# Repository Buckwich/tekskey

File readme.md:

# Tekskey

> WIP This project is still in its prototyping phase

TODO description. Keypoints: modular, hotswap, ARGB, mirage. Usage of git submodules and stow

## Design Process

### Layout Testing with print outs

With [KLE](http://www.keyboard-layout-editor.com/) I came up with a base layout (white):

As I was unsure about the top & bottom design, I included multiple variants. The pcb version should also include support for the light gray variant (PCB A variant), which also allows to use the same pcb for left & right.

More images can be seen in [layouts/](layout/readme.md)

### Handwired 3d printed hotswap prototype

Using the [hotswap PCB generator](https://github.com/50an6xy06r6n/hotswap_pcb_generator) I printed a first prototype which I used and tested for a few weeks. The 3d printed prototype only supports the white layout.

For more renders, source and print files see [prototype](prototype/readme.md)

### QMK firmware (I'm thinking about switching to KMK)

TODO

### PCB Design

TODO

### Pull submodules

```
git submodule update --init --remote --recursive
```

https://raw.githubusercontent.com/ebastler/ebastler-KiCad-repository/main/repository.json

grid {
"name": "MX U 1/32",
"x": "0.5953125",
"y": "0.5953125"
},
{
"name": "MX U 1/24",
"x": "0.79375",
"y": "0.79375"
},
{
"name": "MX U 1/16",
"x": "1.190625",
"y": "1.190625"
},
{
"name": "MX U 1/8",
"x": "2.38125",
"y": "2.38125"
},
{
"name": "MX U 1/4",
"x": "4.7625",
"y": "4.7625"
},
{
"name": "MX U 1/2",
"x": "9.525",
"y": "9.525"
},
{
"name": "MX U 1",
"x": "19.05",
"y": "19.05"
},

TODO

check mcu mirroring

reroute edges

document lib use

find custom buckwich

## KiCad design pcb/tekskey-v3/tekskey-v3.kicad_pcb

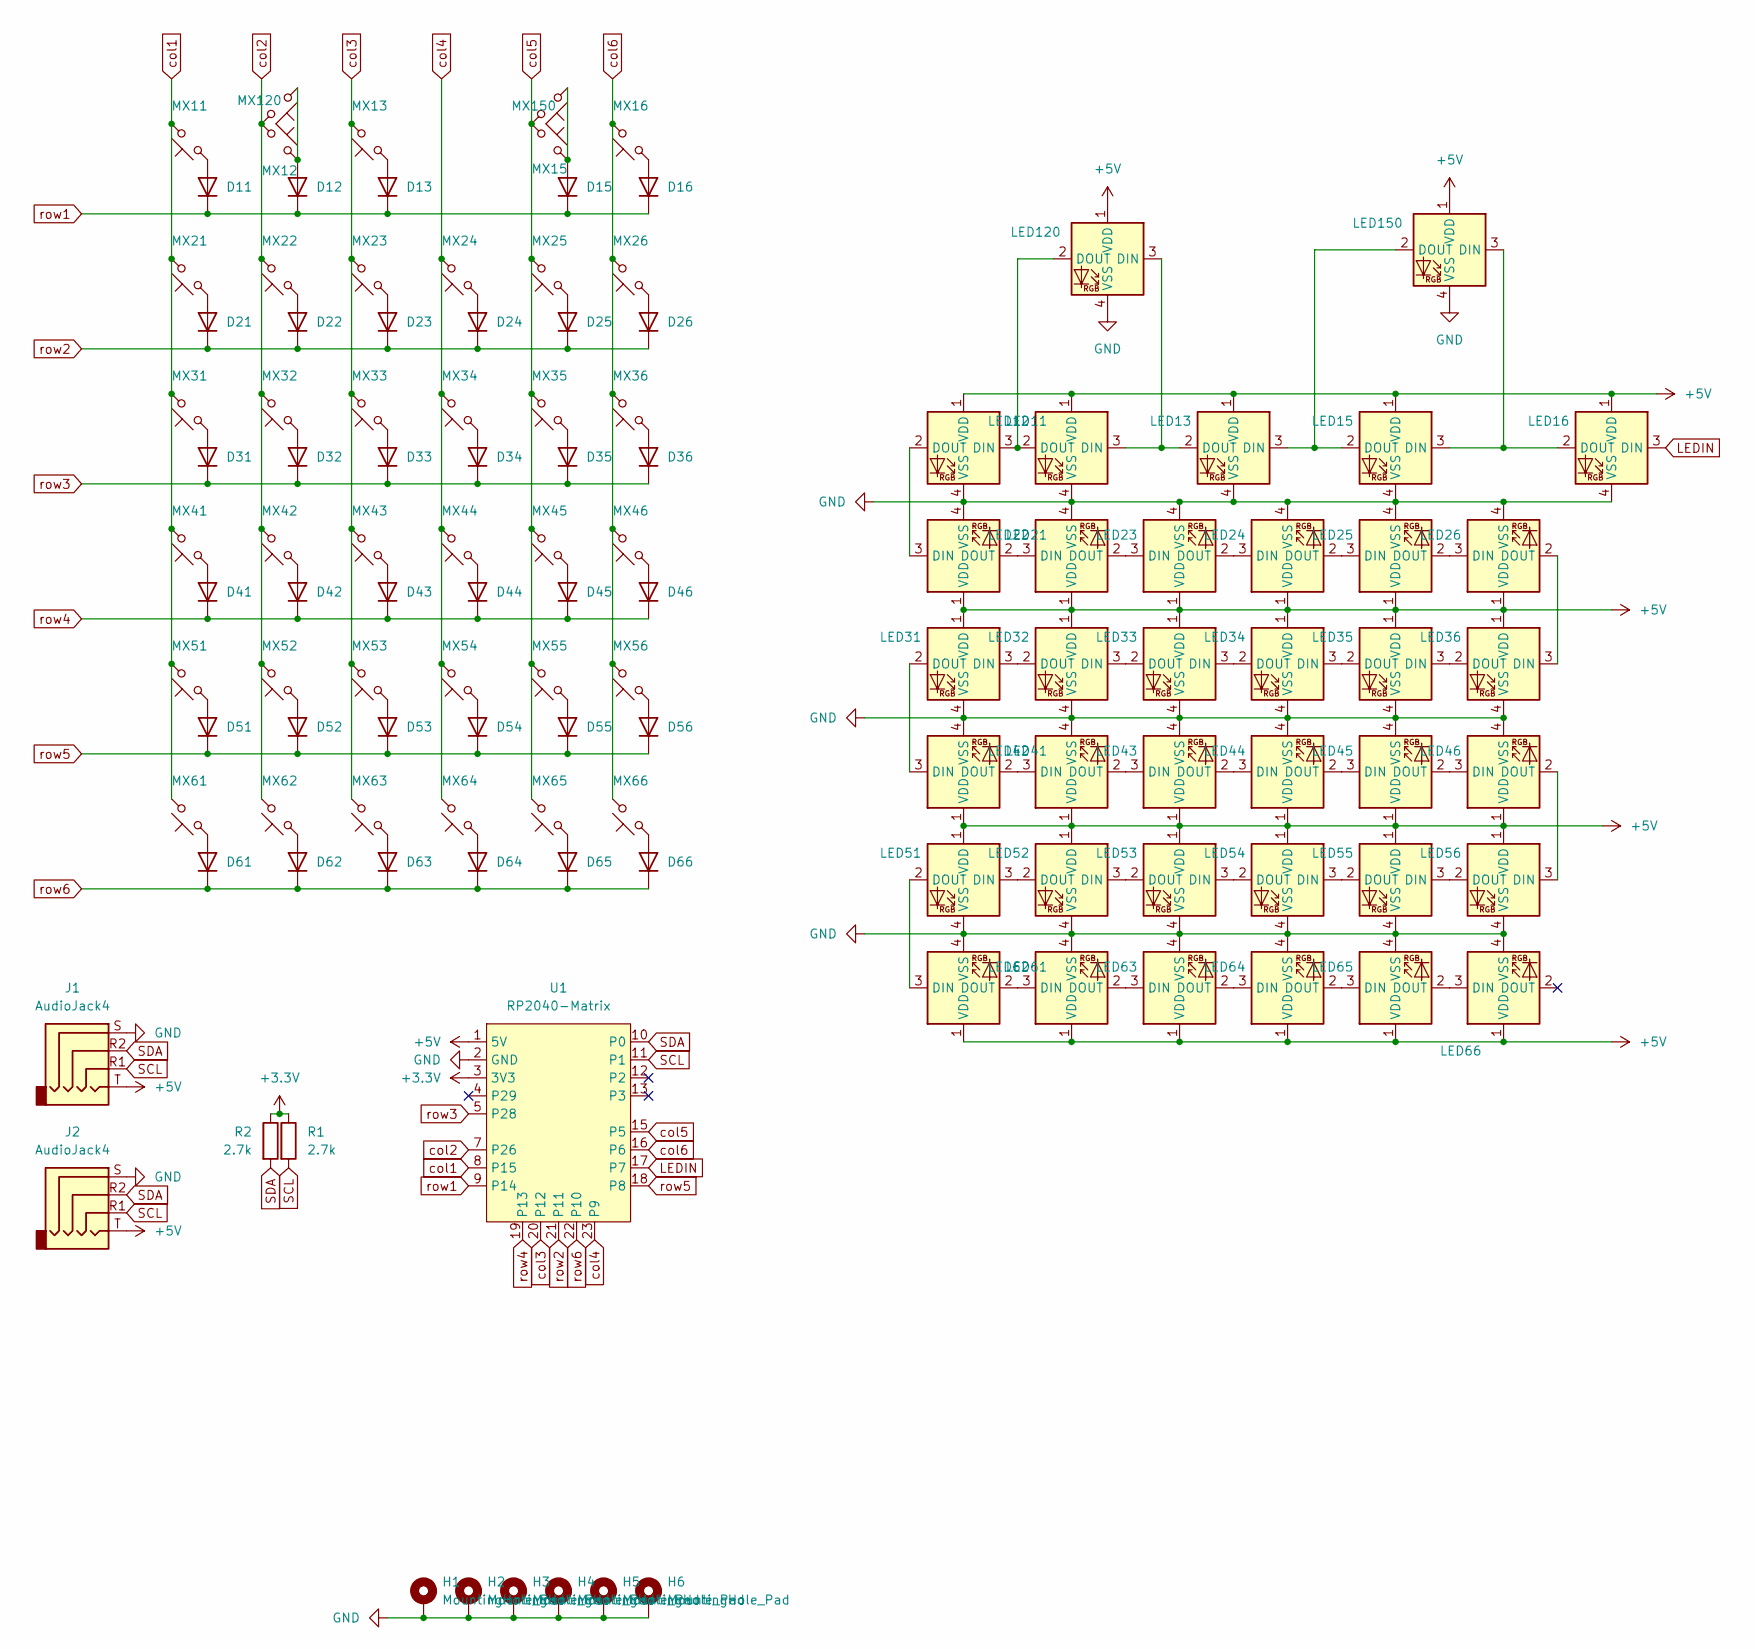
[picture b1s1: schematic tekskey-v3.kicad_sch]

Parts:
D11, D12, D13, D15, D16, D21, D22, D23, D24, D25, D26, D31, D32, D33, D34, D35, D36, D41, D42, D43, D44, D45, D46, D51, D52, D53, D54, D55, D56, D61, D62, D63, D64, D65, D66: D; Hybrid Diode
H1, H2, H3, H4, H5, H6: MountingHole_Pad; MountingHole_2.2mm_M2_Pad_Via
J1, J2: AudioJack4; PJ320A
LED11, LED12, LED13, LED15, LED16, LED31, LED32, LED33, LED34, LED35, LED36, LED51, LED52, LED53, LED54, LED55, LED56, LED120, LED150: MX_SK6812MINI-E; LED_MX_6028R-ROT
LED21, LED22, LED23, LED24, LED25, LED26, LED41, LED42, LED43, LED44, LED45, LED46, LED61, LED62, LED63, LED64, LED65, LED66: MX_SK6812MINI-E; LED_MX_6028R
MX11, MX12, MX13, MX15, MX16, MX21, MX22, MX23, MX24, MX25, MX26, MX31, MX32, MX33, MX34, MX35, MX36, MX41, MX42, MX43, MX44, MX45, MX46, MX51, MX52, MX53, MX54, MX55, MX56, MX61, MX62, MX63, MX64, MX65, MX66, MX120, MX150: MX_SW_HS; SW_MX_HS_CPG151101S11_1u_no-silk
R1, R2: 2.7k; R_1206_3216Metric_Pad1.30x1.75mm_HandSolder
U1: RP2040-Matrix; RP2040-Matrix_AH

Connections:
+3.3V: R1.1, R2.1, U1.3 (3V3)
+5V: J1.T, J2.T, LED11.1 (VDD), LED12.1 (VDD), LED13.1 (VDD), LED15.1 (VDD), LED16.1 (VDD), LED21.1 (VDD), LED22.1 (VDD), LED23.1 (VDD), LED24.1 (VDD), LED25.1 (VDD), LED26.1 (VDD), LED31.1 (VDD), LED32.1 (VDD), LED33.1 (VDD), LED34.1 (VDD), LED35.1 (VDD), LED36.1 (VDD), LED41.1 (VDD), LED42.1 (VDD), LED43.1 (VDD), LED44.1 (VDD), LED45.1 (VDD), LED46.1 (VDD), LED51.1 (VDD), LED52.1 (VDD), LED53.1 (VDD), LED54.1 (VDD), LED55.1 (VDD), LED56.1 (VDD), LED61.1 (VDD), LED62.1 (VDD), LED63.1 (VDD), LED64.1 (VDD), LED65.1 (VDD), LED66.1 (VDD), LED120.1 (VDD), LED150.1 (VDD), U1.1 (5V)
GND: H1.1, H2.1, H3.1, H4.1, H5.1, H6.1, J1.S, J2.S, LED11.4 (VSS), LED12.4 (VSS), LED13.4 (VSS), LED15.4 (VSS), LED16.4 (VSS), LED21.4 (VSS), LED22.4 (VSS), LED23.4 (VSS), LED24.4 (VSS), LED25.4 (VSS), LED26.4 (VSS), LED31.4 (VSS), LED32.4 (VSS), LED33.4 (VSS), LED34.4 (VSS), LED35.4 (VSS), LED36.4 (VSS), LED41.4 (VSS), LED42.4 (VSS), LED43.4 (VSS), LED44.4 (VSS), LED45.4 (VSS), LED46.4 (VSS), LED51.4 (VSS), LED52.4 (VSS), LED53.4 (VSS), LED54.4 (VSS), LED55.4 (VSS), LED56.4 (VSS), LED61.4 (VSS), LED62.4 (VSS), LED63.4 (VSS), LED64.4 (VSS), LED65.4 (VSS), LED66.4 (VSS), LED120.4 (VSS), LED150.4 (VSS), U1.2 (GND)
LEDIN: LED16.3 (DIN), U1.17 (P7)
unnamed: D11.2 (A), MX11.1
unnamed: D12.2 (A), MX12.2, MX120.1
unnamed: D13.2 (A), MX13.1
unnamed: D15.2 (A), MX15.2, MX150.1
unnamed: D16.2 (A), MX16.1
unnamed: D21.2 (A), MX21.1
unnamed: D22.2 (A), MX22.1
unnamed: D23.2 (A), MX23.1
unnamed: D24.2 (A), MX24.1
unnamed: D25.2 (A), MX25.1
unnamed: D26.2 (A), MX26.1
unnamed: D31.2 (A), MX31.1
unnamed: D32.2 (A), MX32.1
unnamed: D33.2 (A), MX33.1
unnamed: D34.2 (A), MX34.1
unnamed: D35.2 (A), MX35.1
unnamed: D36.2 (A), MX36.1
unnamed: D41.2 (A), MX41.1
unnamed: D42.2 (A), MX42.1
unnamed: D43.2 (A), MX43.1
unnamed: D44.2 (A), MX44.1
unnamed: D45.2 (A), MX45.1
unnamed: D46.2 (A), MX46.1
unnamed: D51.2 (A), MX51.1
unnamed: D52.2 (A), MX52.1
unnamed: D53.2 (A), MX53.1
unnamed: D54.2 (A), MX54.1
unnamed: D55.2 (A), MX55.1
unnamed: D56.2 (A), MX56.1
unnamed: D61.2 (A), MX61.1
unnamed: D62.2 (A), MX62.1
unnamed: D63.2 (A), MX63.1
unnamed: D64.2 (A), MX64.1
unnamed: D65.2 (A), MX65.1
unnamed: D66.2 (A), MX66.1
unnamed: LED11.3 (DIN), LED12.2 (DOUT), LED120.2 (DOUT)
unnamed: LED11.2 (DOUT), LED21.3 (DIN)
unnamed: LED12.3 (DIN), LED13.2 (DOUT), LED120.3 (DIN)
unnamed: LED13.3 (DIN), LED15.2 (DOUT), LED150.2 (DOUT)
unnamed: LED15.3 (DIN), LED16.2 (DOUT), LED150.3 (DIN)
unnamed: LED21.2 (DOUT), LED22.3 (DIN)
unnamed: LED22.2 (DOUT), LED23.3 (DIN)
unnamed: LED23.2 (DOUT), LED24.3 (DIN)
unnamed: LED24.2 (DOUT), LED25.3 (DIN)
unnamed: LED25.2 (DOUT), LED26.3 (DIN)
unnamed: LED26.2 (DOUT), LED36.3 (DIN)
unnamed: LED31.3 (DIN), LED32.2 (DOUT)
unnamed: LED31.2 (DOUT), LED41.3 (DIN)
unnamed: LED32.3 (DIN), LED33.2 (DOUT)
unnamed: LED33.3 (DIN), LED34.2 (DOUT)
unnamed: LED34.3 (DIN), LED35.2 (DOUT)
unnamed: LED35.3 (DIN), LED36.2 (DOUT)
unnamed: LED41.2 (DOUT), LED42.3 (DIN)
unnamed: LED42.2 (DOUT), LED43.3 (DIN)
unnamed: LED43.2 (DOUT), LED44.3 (DIN)
unnamed: LED44.2 (DOUT), LED45.3 (DIN)
unnamed: LED45.2 (DOUT), LED46.3 (DIN)
unnamed: LED46.2 (DOUT), LED56.3 (DIN)
unnamed: LED51.3 (DIN), LED52.2 (DOUT)
unnamed: LED51.2 (DOUT), LED61.3 (DIN)
unnamed: LED52.3 (DIN), LED53.2 (DOUT)
unnamed: LED53.3 (DIN), LED54.2 (DOUT)
unnamed: LED54.3 (DIN), LED55.2 (DOUT)
unnamed: LED55.3 (DIN), LED56.2 (DOUT)
unnamed: LED61.2 (DOUT), LED62.3 (DIN)
unnamed: LED62.2 (DOUT), LED63.3 (DIN)
unnamed: LED63.2 (DOUT), LED64.3 (DIN)
unnamed: LED64.2 (DOUT), LED65.3 (DIN)
unnamed: LED65.2 (DOUT), LED66.3 (DIN)
SCL: J1.R1, J2.R1, R1.2, U1.11 (P1)
SDA: J1.R2, J2.R2, R2.2, U1.10 (P0)
col1: MX11.2, MX21.2, MX31.2, MX41.2, MX51.2, MX61.2, U1.8 (P15)
col2: MX12.1, MX22.2, MX32.2, MX42.2, MX52.2, MX62.2, MX120.2, U1.7 (P26)
col3: MX13.2, MX23.2, MX33.2, MX43.2, MX53.2, MX63.2, U1.20 (P12)
col4: MX24.2, MX34.2, MX44.2, MX54.2, MX64.2, U1.23 (P9)
col5: MX15.1, MX25.2, MX35.2, MX45.2, MX55.2, MX65.2, MX150.2, U1.15 (P5)
col6: MX16.2, MX26.2, MX36.2, MX46.2, MX56.2, MX66.2, U1.16 (P6)
row1: D11.1 (K), D12.1 (K), D13.1 (K), D15.1 (K), D16.1 (K), U1.9 (P14)
row2: D21.1 (K), D22.1 (K), D23.1 (K), D24.1 (K), D25.1 (K), D26.1 (K), U1.21 (P11)
row3: D31.1 (K), D32.1 (K), D33.1 (K), D34.1 (K), D35.1 (K), D36.1 (K), U1.5 (P28)
row4: D41.1 (K), D42.1 (K), D43.1 (K), D44.1 (K), D45.1 (K), D46.1 (K), U1.19 (P13)
row5: D51.1 (K), D52.1 (K), D53.1 (K), D54.1 (K), D55.1 (K), D56.1 (K), U1.18 (P8)
row6: D61.1 (K), D62.1 (K), D63.1 (K), D64.1 (K), D65.1 (K), D66.1 (K), U1.22 (P10)

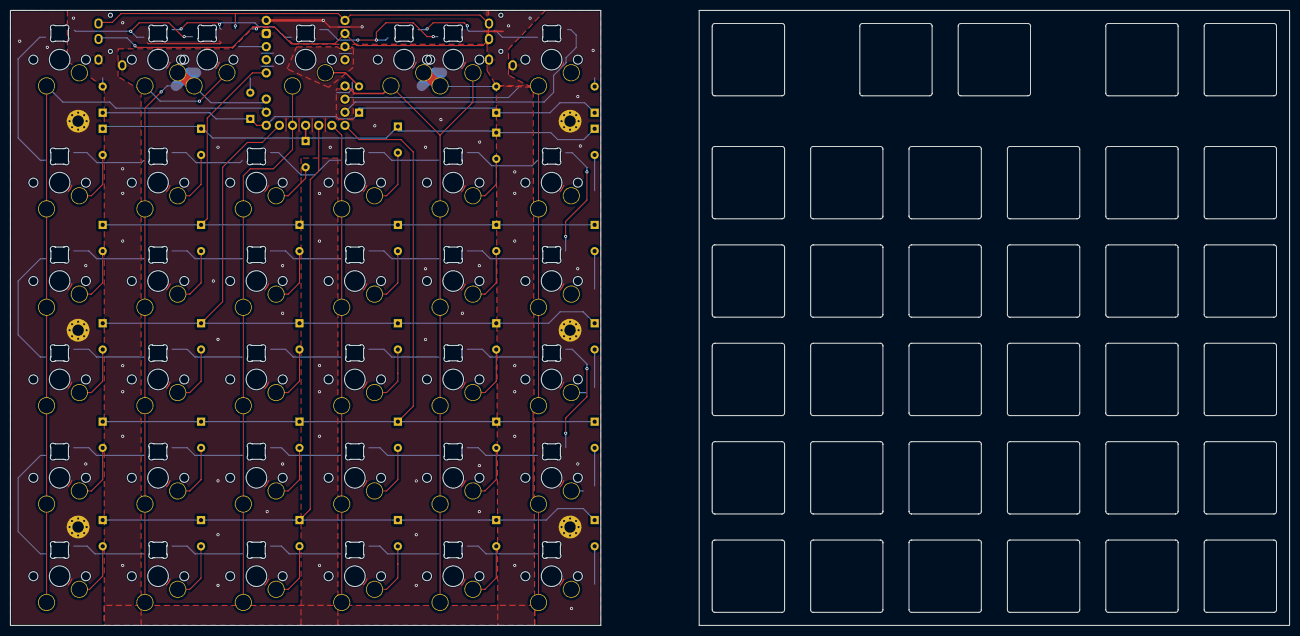
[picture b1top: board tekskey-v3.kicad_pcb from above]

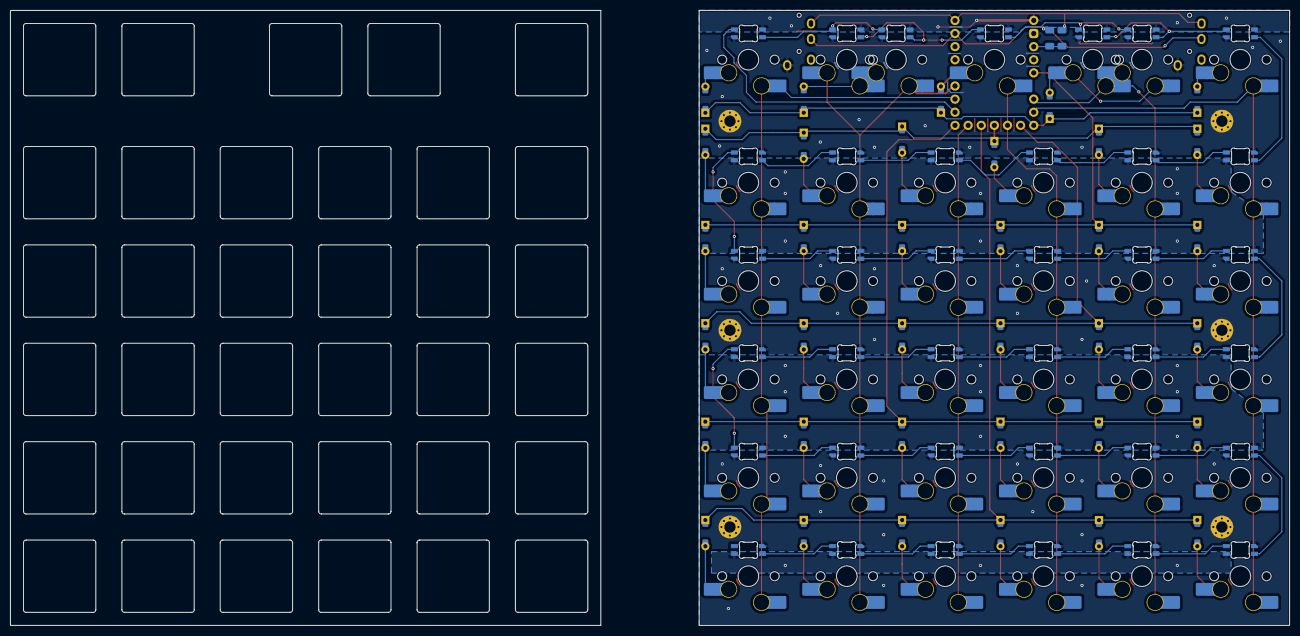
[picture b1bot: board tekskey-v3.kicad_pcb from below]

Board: 2 copper layers, 247.6 x 119.0 mm, 120 parts (113 on the bottom side), 87 nets.

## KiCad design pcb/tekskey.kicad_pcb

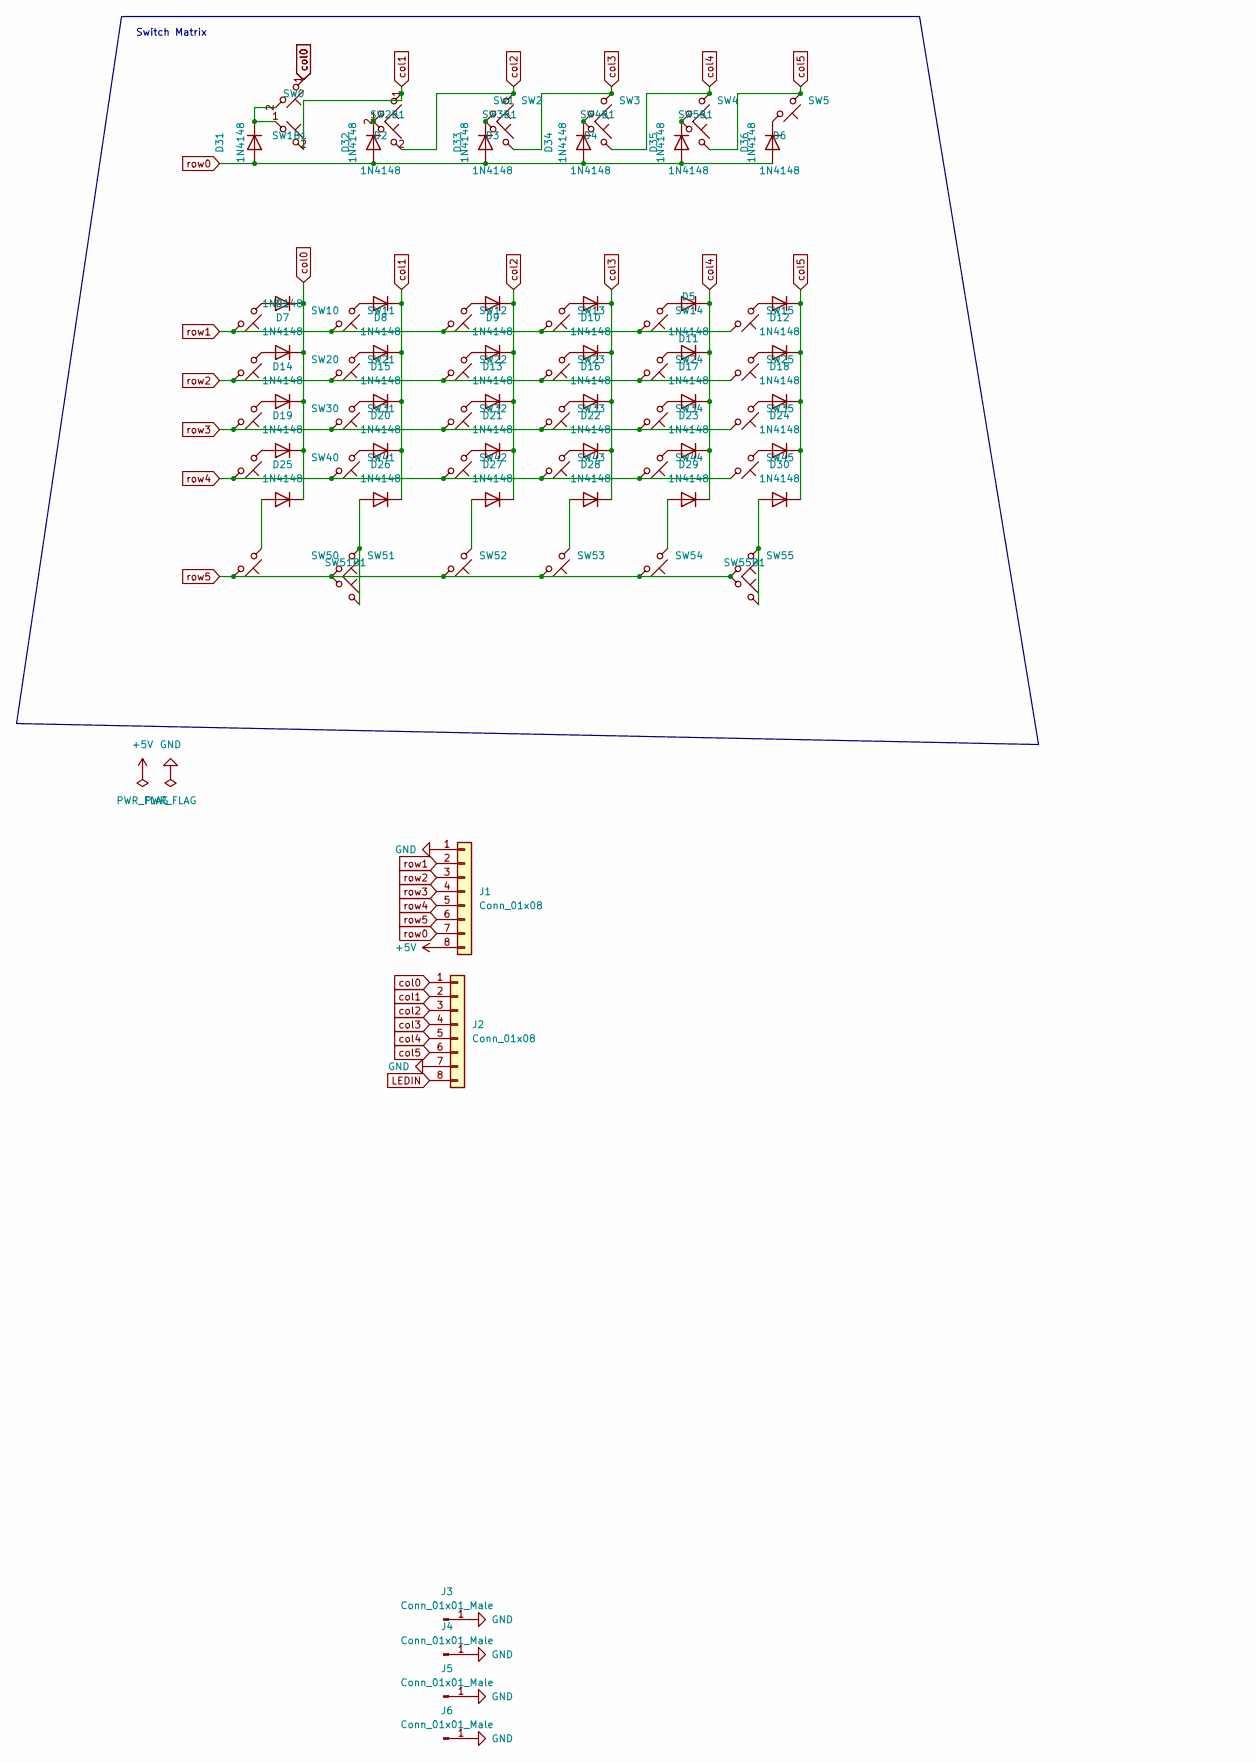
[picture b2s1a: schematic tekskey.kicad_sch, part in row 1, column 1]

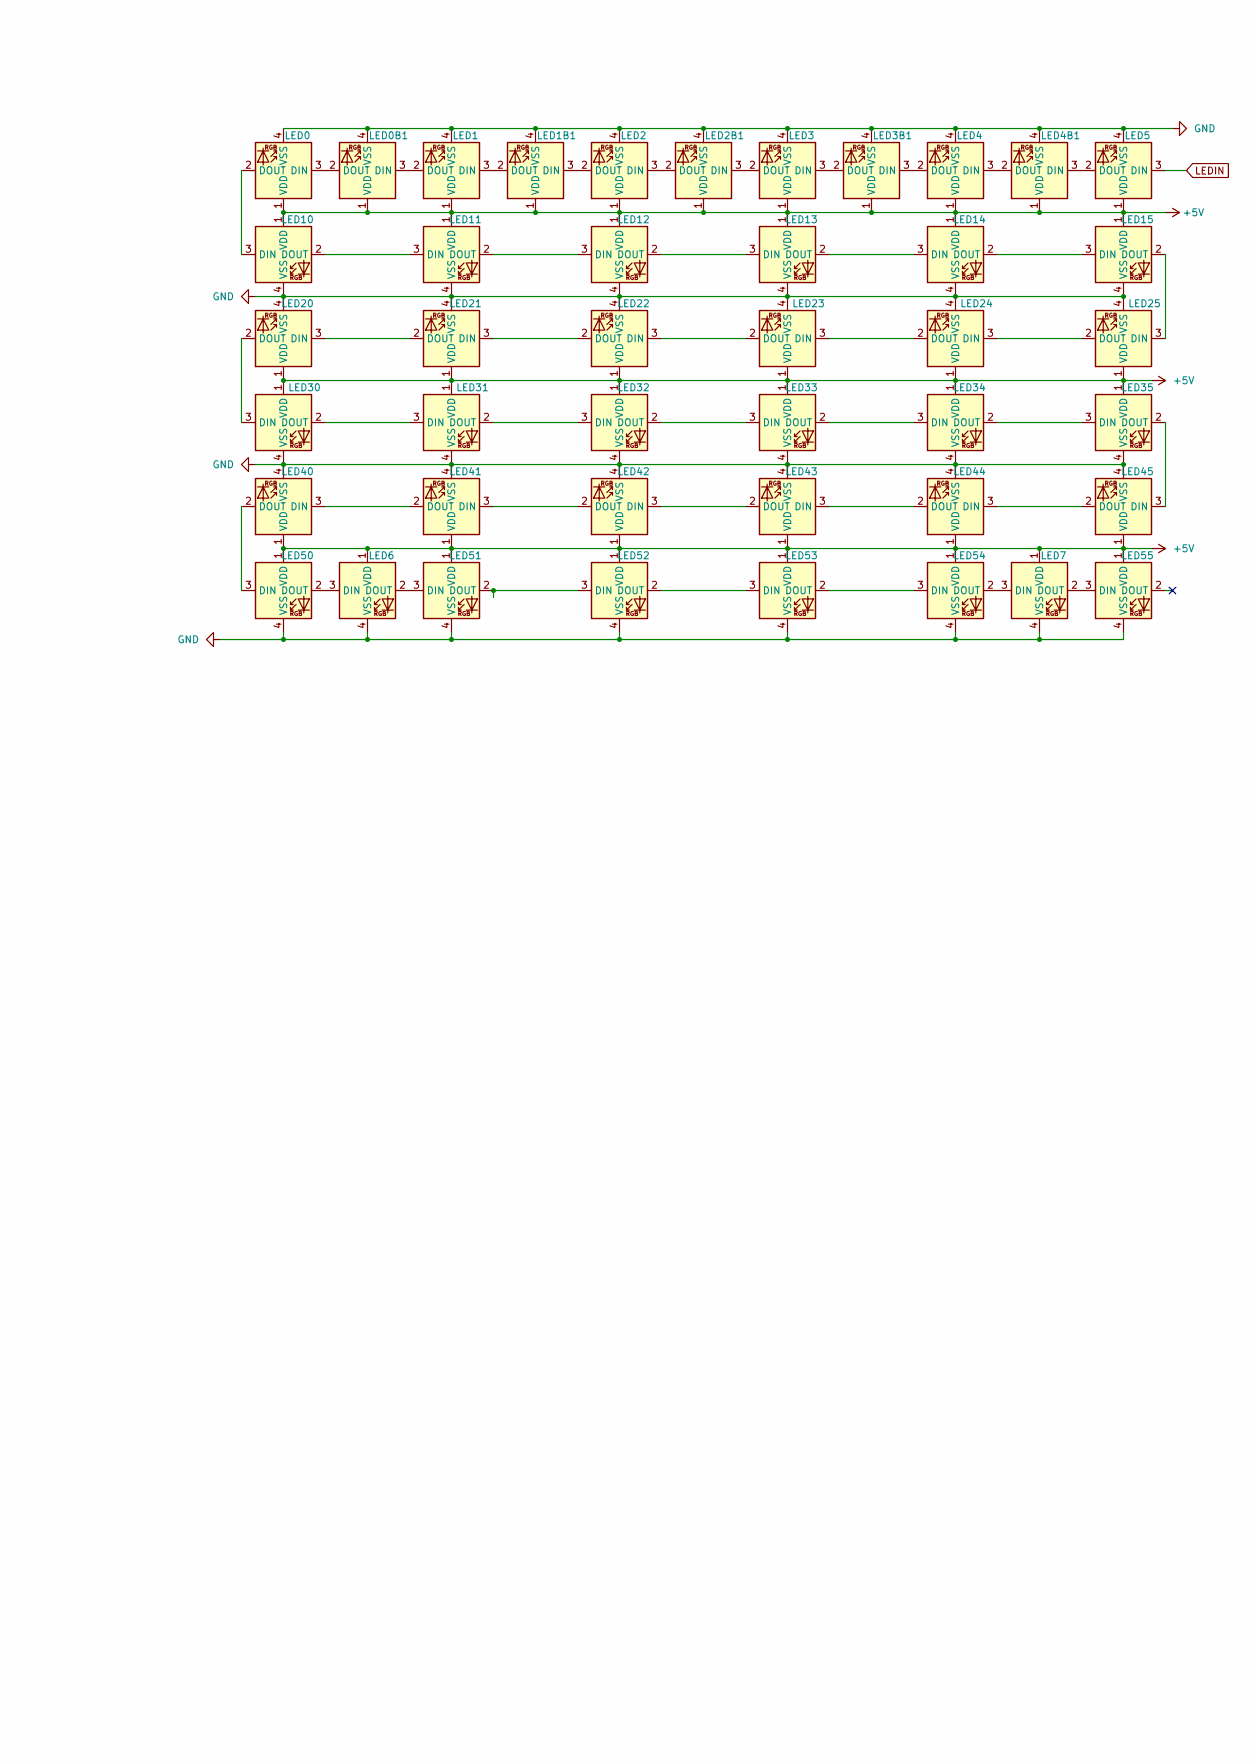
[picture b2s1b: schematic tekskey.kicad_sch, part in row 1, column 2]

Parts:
D1, D2, D3, D4, D5, D6, D7, D8, D9, D10, D11, D12, D13, D14, D15, D16, D17, D18, D19, D20, D21, D22, D23, D24, D25, D26, D27, D28, D29, D30, D31, D32, D33, D34, D35, D36: 1N4148; D_DO-35_SOD27_P7.62mm_Horizontal_NoSilk
J1, J2: Conn_01x08; PinHeader_1x08_P2.54mm_Vertical
J3, J4, J5, J6: Conn_01x01_Male; MountingHole_3.2mm_M3_DIN965_Pad
LED0, LED0B1, LED1, LED1B1, LED2, LED2B1, LED3, LED3B1, LED4, LED4B1, LED5, LED20, LED21, LED22, LED23, LED24, LED25, LED40, LED41, LED42, LED43, LED44, LED45: MX_SK6812MINI-E; LED_MX_6028R
LED6, LED7, LED10, LED11, LED12, LED13, LED14, LED15, LED30, LED31, LED32, LED33, LED34, LED35, LED50, LED51, LED52, LED53, LED54, LED55: MX_SK6812MINI-E; LED_MX_6028R-FLIPPED
SW0, SW1, SW1B1, SW2, SW2B1, SW3, SW3B1, SW4, SW4B1, SW5, SW5B1, SW10, SW11, SW12, SW13, SW14, SW15, SW20, SW21, SW22, SW23, SW24, SW25, SW30, SW31, SW32, SW33, SW34, SW35, SW40, SW41, SW42, SW43, SW44, SW45, SW50, SW51, SW51B1, SW52, SW53, SW54, SW55, SW55B1: MX_SW_HS; SW_MX_HS_1u

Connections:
+5V: J1.8, LED0.1 (VDD), LED0B1.1 (VDD), LED1.1 (VDD), LED1B1.1 (VDD), LED2.1 (VDD), LED2B1.1 (VDD), LED3.1 (VDD), LED3B1.1 (VDD), LED4.1 (VDD), LED4B1.1 (VDD), LED5.1 (VDD), LED6.1 (VDD), LED7.1 (VDD), LED10.1 (VDD), LED11.1 (VDD), LED12.1 (VDD), LED13.1 (VDD), LED14.1 (VDD), LED15.1 (VDD), LED20.1 (VDD), LED21.1 (VDD), LED22.1 (VDD), LED23.1 (VDD), LED24.1 (VDD), LED25.1 (VDD), LED30.1 (VDD), LED31.1 (VDD), LED32.1 (VDD), LED33.1 (VDD), LED34.1 (VDD), LED35.1 (VDD), LED40.1 (VDD), LED41.1 (VDD), LED42.1 (VDD), LED43.1 (VDD), LED44.1 (VDD), LED45.1 (VDD), LED50.1 (VDD), LED51.1 (VDD), LED52.1 (VDD), LED53.1 (VDD), LED54.1 (VDD), LED55.1 (VDD)
GND: J1.1, J2.7, J3.1, J4.1, J5.1, J6.1, LED0.4 (VSS), LED0B1.4 (VSS), LED1.4 (VSS), LED1B1.4 (VSS), LED2.4 (VSS), LED2B1.4 (VSS), LED3.4 (VSS), LED3B1.4 (VSS), LED4.4 (VSS), LED4B1.4 (VSS), LED5.4 (VSS), LED6.4 (VSS), LED7.4 (VSS), LED10.4 (VSS), LED11.4 (VSS), LED12.4 (VSS), LED13.4 (VSS), LED14.4 (VSS), LED15.4 (VSS), LED20.4 (VSS), LED21.4 (VSS), LED22.4 (VSS), LED23.4 (VSS), LED24.4 (VSS), LED25.4 (VSS), LED30.4 (VSS), LED31.4 (VSS), LED32.4 (VSS), LED33.4 (VSS), LED34.4 (VSS), LED35.4 (VSS), LED40.4 (VSS), LED41.4 (VSS), LED42.4 (VSS), LED43.4 (VSS), LED44.4 (VSS), LED45.4 (VSS), LED50.4 (VSS), LED51.4 (VSS), LED52.4 (VSS), LED53.4 (VSS), LED54.4 (VSS), LED55.4 (VSS)
LEDIN: J2.8, LED5.3 (DIN)
unnamed: D1.2 (A), SW10.1
unnamed: D2.2 (A), SW11.1
unnamed: D3.2 (A), SW12.1
unnamed: D4.2 (A), SW13.1
unnamed: D5.2 (A), SW14.1
unnamed: D6.2 (A), SW15.1
unnamed: D7.2 (A), SW20.1
unnamed: D8.2 (A), SW21.1
unnamed: D9.2 (A), SW22.1
unnamed: D10.2 (A), SW23.1
unnamed: D11.2 (A), SW24.1
unnamed: D12.2 (A), SW25.1
unnamed: D13.2 (A), SW32.1
unnamed: D14.2 (A), SW30.1
unnamed: D15.2 (A), SW31.1
unnamed: D16.2 (A), SW33.1
unnamed: D17.2 (A), SW34.1
unnamed: D18.2 (A), SW35.1
unnamed: D19.2 (A), SW40.1
unnamed: D20.2 (A), SW41.1
unnamed: D21.2 (A), SW42.1
unnamed: D22.2 (A), SW43.1
unnamed: D23.2 (A), SW44.1
unnamed: D24.2 (A), SW45.1
unnamed: D25.2 (A), SW50.1
unnamed: D26.2 (A), SW51.1, SW51B1.2
unnamed: D27.2 (A), SW52.1
unnamed: D28.2 (A), SW53.1
unnamed: D29.2 (A), SW54.1
unnamed: D30.2 (A), SW55.1, SW55B1.2
unnamed: D31.1 (K), SW0.2, SW1B1.1
unnamed: D32.1 (K), SW1.2, SW2B1.1
unnamed: D33.1 (K), SW2.2, SW3B1.1
unnamed: D34.1 (K), SW3.2, SW4B1.1
unnamed: D35.1 (K), SW4.2, SW5B1.1
unnamed: D36.1 (K), SW5.2
unnamed: LED0.2 (DOUT), LED10.3 (DIN)
unnamed: LED0.3 (DIN), LED0B1.2 (DOUT)
unnamed: LED0B1.3 (DIN), LED1.2 (DOUT)
unnamed: LED1.3 (DIN), LED1B1.2 (DOUT)
unnamed: LED1B1.3 (DIN), LED2.2 (DOUT)
unnamed: LED2.3 (DIN), LED2B1.2 (DOUT)
unnamed: LED2B1.3 (DIN), LED3.2 (DOUT)
unnamed: LED3.3 (DIN), LED3B1.2 (DOUT)
unnamed: LED3B1.3 (DIN), LED4.2 (DOUT)
unnamed: LED4.3 (DIN), LED4B1.2 (DOUT)
unnamed: LED4B1.3 (DIN), LED5.2 (DOUT)
unnamed: LED10.2 (DOUT), LED11.3 (DIN)
unnamed: LED11.2 (DOUT), LED12.3 (DIN)
unnamed: LED12.2 (DOUT), LED13.3 (DIN)
unnamed: LED13.2 (DOUT), LED14.3 (DIN)
unnamed: LED14.2 (DOUT), LED15.3 (DIN)
unnamed: LED15.2 (DOUT), LED25.3 (DIN)
unnamed: LED20.2 (DOUT), LED30.3 (DIN)
unnamed: LED20.3 (DIN), LED21.2 (DOUT)
unnamed: LED21.3 (DIN), LED22.2 (DOUT)
unnamed: LED22.3 (DIN), LED23.2 (DOUT)
unnamed: LED23.3 (DIN), LED24.2 (DOUT)
unnamed: LED24.3 (DIN), LED25.2 (DOUT)
unnamed: LED30.2 (DOUT), LED31.3 (DIN)
unnamed: LED31.2 (DOUT), LED32.3 (DIN)
unnamed: LED32.2 (DOUT), LED33.3 (DIN)
unnamed: LED33.2 (DOUT), LED34.3 (DIN)
unnamed: LED34.2 (DOUT), LED35.3 (DIN)
unnamed: LED35.2 (DOUT), LED45.3 (DIN)
unnamed: LED40.2 (DOUT), LED50.3 (DIN)
unnamed: LED40.3 (DIN), LED41.2 (DOUT)
unnamed: LED41.3 (DIN), LED42.2 (DOUT)
unnamed: LED42.3 (DIN), LED43.2 (DOUT)
unnamed: LED43.3 (DIN), LED44.2 (DOUT)
unnamed: LED44.3 (DIN), LED45.2 (DOUT)
unnamed: LED6.3 (DIN), LED50.2 (DOUT)
unnamed: LED51.2 (DOUT), LED52.3 (DIN)
unnamed: LED6.2 (DOUT), LED51.3 (DIN)
unnamed: LED52.2 (DOUT), LED53.3 (DIN)
unnamed: LED53.2 (DOUT), LED54.3 (DIN)
unnamed: LED7.3 (DIN), LED54.2 (DOUT)
unnamed: LED7.2 (DOUT), LED55.3 (DIN)
col0: D1.1 (K), D7.1 (K), D14.1 (K), D19.1 (K), D25.1 (K), J2.1, SW0.1
col1: D2.1 (K), D8.1 (K), D15.1 (K), D20.1 (K), D26.1 (K), J2.2, SW1.1, SW1B1.2
col2: D3.1 (K), D9.1 (K), D13.1 (K), D21.1 (K), D27.1 (K), J2.3, SW2.1, SW2B1.2
col3: D4.1 (K), D10.1 (K), D16.1 (K), D22.1 (K), D28.1 (K), J2.4, SW3.1, SW3B1.2
col4: D5.1 (K), D11.1 (K), D17.1 (K), D23.1 (K), D29.1 (K), J2.5, SW4.1, SW4B1.2
col5: D6.1 (K), D12.1 (K), D18.1 (K), D24.1 (K), D30.1 (K), J2.6, SW5.1, SW5B1.2
row0: D31.2 (A), D32.2 (A), D33.2 (A), D34.2 (A), D35.2 (A), D36.2 (A), J1.7
row1: J1.2, SW10.2, SW11.2, SW12.2, SW13.2, SW14.2, SW15.2
row2: J1.3, SW20.2, SW21.2, SW22.2, SW23.2, SW24.2, SW25.2
row3: J1.4, SW30.2, SW31.2, SW32.2, SW33.2, SW34.2, SW35.2
row4: J1.5, SW40.2, SW41.2, SW42.2, SW43.2, SW44.2, SW45.2
row5: J1.6, SW50.2, SW51.2, SW51B1.1, SW52.2, SW53.2, SW54.2, SW55.2, SW55B1.1

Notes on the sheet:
Switch Matrix

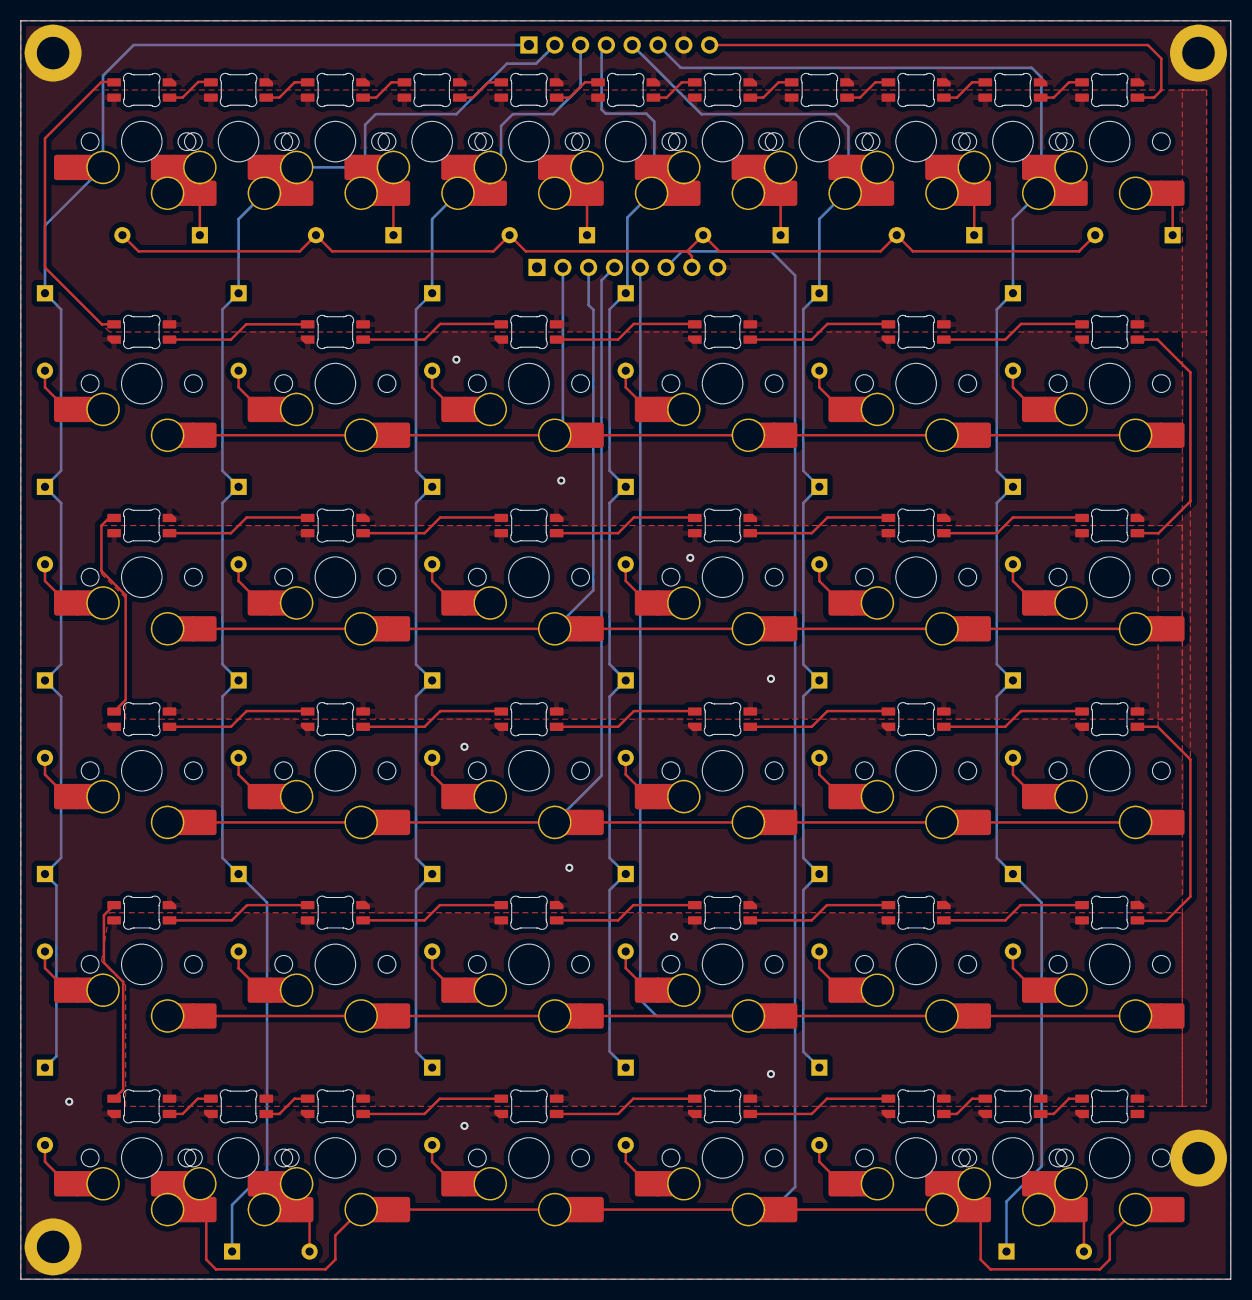
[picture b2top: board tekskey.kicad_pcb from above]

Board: 2 copper layers, 119.1 x 123.8 mm, 128 parts (0 on the bottom side), 93 nets.

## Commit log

2022-11-13 init
2022-11-13 add layouts
2022-11-20 init pcb. Issues:
    south facing leds
2022-11-20 rotate each key
2022-11-20 add spacing to f row
2022-11-20 add led jumper
2022-11-20 remove some jumpers
2022-11-20 add through hole diodes
2022-11-26 align switches
2022-11-26 fix diode assignment
2022-11-26 cleanup routing
2022-11-26 use zones for power
2022-12-03 add rounded
2022-12-11 order v1
2023-07-07 adjustments
2024-01-31 pcb v2
2024-01-31 refine vision
